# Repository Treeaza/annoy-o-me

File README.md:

# annoy-o-me
 Cheap and compacy AVR-based noisemaker

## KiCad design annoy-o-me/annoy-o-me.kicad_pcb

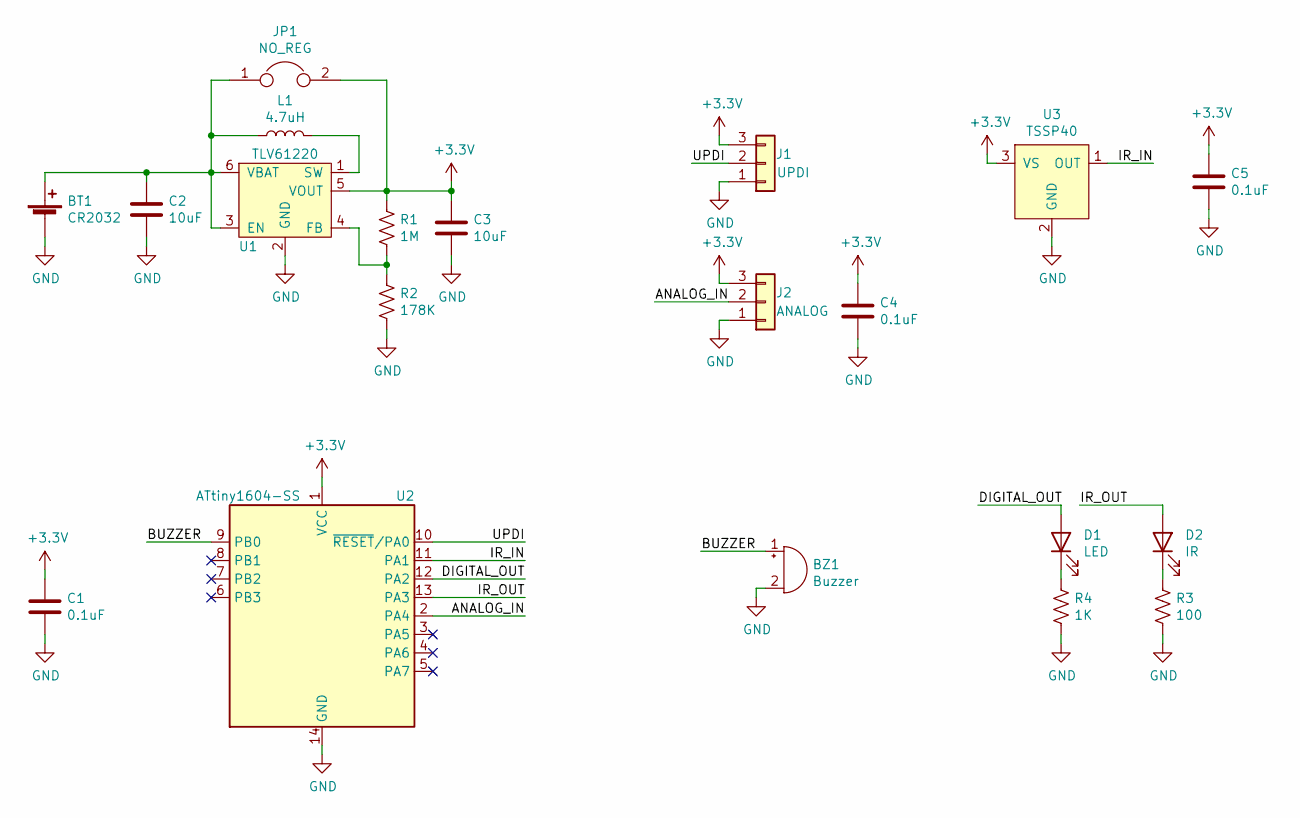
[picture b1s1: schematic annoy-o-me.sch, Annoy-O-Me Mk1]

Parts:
BT1: CR2032; BatteryHolder_Keystone_3002_1x2032
BZ1: Buzzer; Buzzer_15x7.5RM7.6
C1, C4, C5: 0.1uF; C_0603_1608Metric_Pad1.08x0.95mm_HandSolder
C2, C3: 10uF; C_1210_3225Metric_Pad1.33x2.70mm_HandSolder
D1: LED; LED_0805_2012Metric_Pad1.15x1.40mm_HandSolder
D2: IR; LED_D5.0mm
J1: UPDI; PinHeader_1x03_P2.54mm_Vertical
J2: ANALOG; PinHeader_1x03_P2.54mm_Vertical
JP1: NO_REG; SolderJumper-2_P1.3mm_Open_RoundedPad1.0x1.5mm
L1: 4.7uH; L_0805_2012Metric_Pad1.15x1.40mm_HandSolder
R1: 1M; R_0603_1608Metric_Pad0.98x0.95mm_HandSolder
R2: 178K; R_0603_1608Metric_Pad0.98x0.95mm_HandSolder
R3: 100; R_0603_1608Metric_Pad0.98x0.95mm_HandSolder
R4: 1K; R_0603_1608Metric_Pad0.98x0.95mm_HandSolder
U1: TLV61220; SOT-23-6_Handsoldering
U2: ATtiny1604-SS; SOIC-14_3.9x8.7mm_P1.27mm
U3: TSSP40; PinHeader_1x03_P2.54mm_Vertical

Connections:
+3V3: C1.1, C3.1, C4.1, C5.1, J1.3, J2.3, JP1.2, R1.1, U1.5 (VOUT), U2.1 (VCC), U3.3 (VS)
/ANALOG_IN: J2.2, U2.2 (PA4)
/BUZZER: BZ1.1 (-), U2.9 (PB0)
/DIGITAL_OUT: D1.2 (A), U2.12 (PA2)
/IR_IN: U2.11 (PA1), U3.1 (OUT)
/IR_OUT: D2.2 (A), U2.13 (PA3)
/UPDI: J1.2, U2.10 (~RESET~/PA0)
GND: BT1.2 (-), BZ1.2 (+), C1.2, C2.2, C3.2, C4.2, C5.2, J1.1, J2.1, R2.2, R3.2, R4.2, U1.2 (GND), U2.14 (GND), U3.2 (GND)
unnamed: BT1.1 (+), C2.1, JP1.1, L1.1, U1.3 (EN), U1.6 (VBAT)
unnamed: D1.1 (K), R4.1
unnamed: D2.1 (K), R3.1
unnamed: L1.2, U1.1 (SW)
unnamed: R1.2, R2.1, U1.4 (FB)

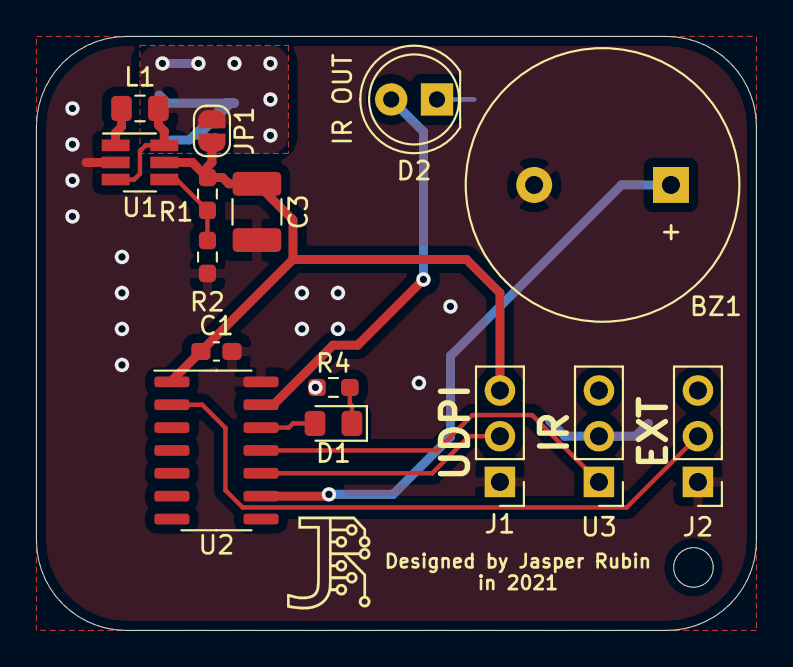
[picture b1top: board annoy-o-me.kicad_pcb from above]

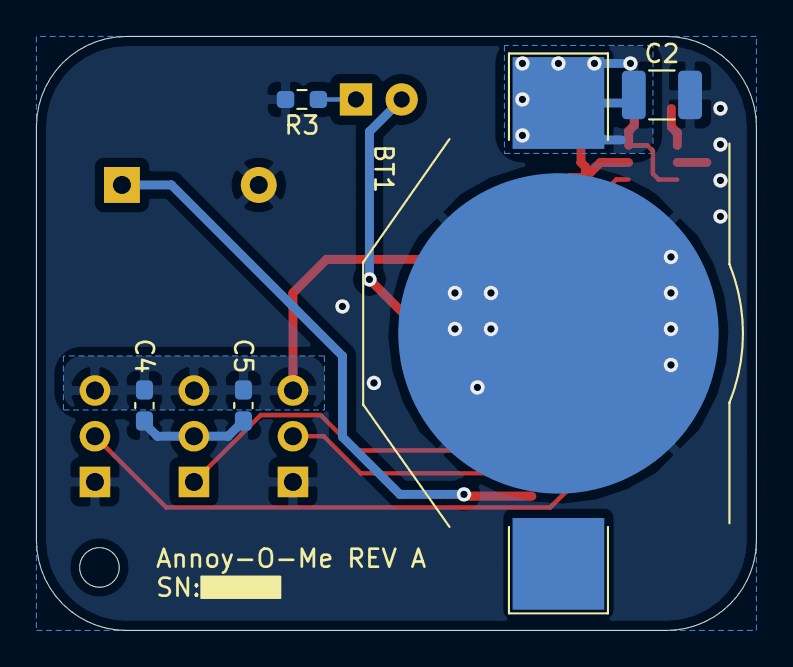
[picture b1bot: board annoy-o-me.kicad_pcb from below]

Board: 2 copper layers, 40.0 x 33.0 mm, 20 parts (5 on the bottom side), 13 nets.

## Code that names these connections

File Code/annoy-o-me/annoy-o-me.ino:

// Firmware for the annoy-o-me ATtiny noisemaker by Jasper Rubin (jasperrubin.com)
// https://github.com/Treeaza/annoy-o-me
// This code is free to use but includes no waranty, gurantee of functionality, or support
// Copyright 2021, Jasper Rubin
// All rights reserved


// ---------- PARAMETERS ----------

// bits are (LSB first):
// 1: heartbeat on/off
// 2-4: currently unused, may be used in future for heartbeat types
// 5: recovery tone on/off
// 6: 
// 7:
// 8:
//PROGMEM const byte SYSTEM_TOGGLES = 0b00000000;
//
//#define ST_HEARTBEAT_EN 0b00000001
//#define ST_HEARTBEAT_TYPE 0b00001110
//#define ST_RECOVERY_EN 0b00010000

// ^^^^^^^^^^ END PARAMETERS ^^^^^^^^^^

#define BUZZER_PIN 7
//#define IR_IN_PIN 8
//#define ANALOG_IN_PIN 0
//#define IR_OUT_PIN 10
//#define DIGITAL_OUT_PIN 9

//volatile bool validHeartbeat;

// ---------- FUNCTION PROTOTYPES ----------

void sleepSeconds(unsigned long);

//void interruptHeartbeatISR();
//void startHeartbeat_digitalVoltage(int, int);
//bool verifyHeartbeat_digitalVoltage(int);

// ^^^^^^^^^^ END FUNCTION PROTOTOTYPES ^^^^^^^^^^

// --------- SLEEP ----------

// Sleep for specified duration in seconds (roughly)
void sleepSeconds(unsigned long seconds){
  
}

// ^^^^^^^^^^ END SLEEP ^^^^^^^^^^

// ---------- HEARTBEAT ----------

// Generic heartbeat failure ISR
//void interruptHeartbeatISR(){
//  validHeartbeat = false;
//}

// Start digital voltage heartbeat
//void startHeartbeat_digitalVoltage(int inPin){
//  // set pinmodes and start heartbeat
//  pinMode(inPin, INPUT);
//
//  // set up interrupt
//  attachInterrupt(digitalPinToInterrupt(inPin), interruptHeartbeatISR, FALLING);
//  
//  validHeartbeat = true;
//}
//
//// Verify digital voltage heartbeat
//bool verifyHeartbeat_digitalVoltage(int inPin){
//  return digitalRead(inPin);
//}

// ^^^^^^^^^^ END HEARTBEAT ^^^^^^^^^^

// ---------- MAIN CODE ----------

void setup(){
  pinMode(BUZZER_PIN, OUTPUT);
  delay(5000);
}

void loop(){
  tone(BUZZER_PIN, 2000);
  delay(500);
  noTone(BUZZER_PIN);
  delay(1000);
}

// ^^^^^^^^^^ END MAIN CODE ^^^^^^^^^^

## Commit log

2021-02-26 Board design
2021-03-14 Work on firmware
2023-03-18 SOme work
